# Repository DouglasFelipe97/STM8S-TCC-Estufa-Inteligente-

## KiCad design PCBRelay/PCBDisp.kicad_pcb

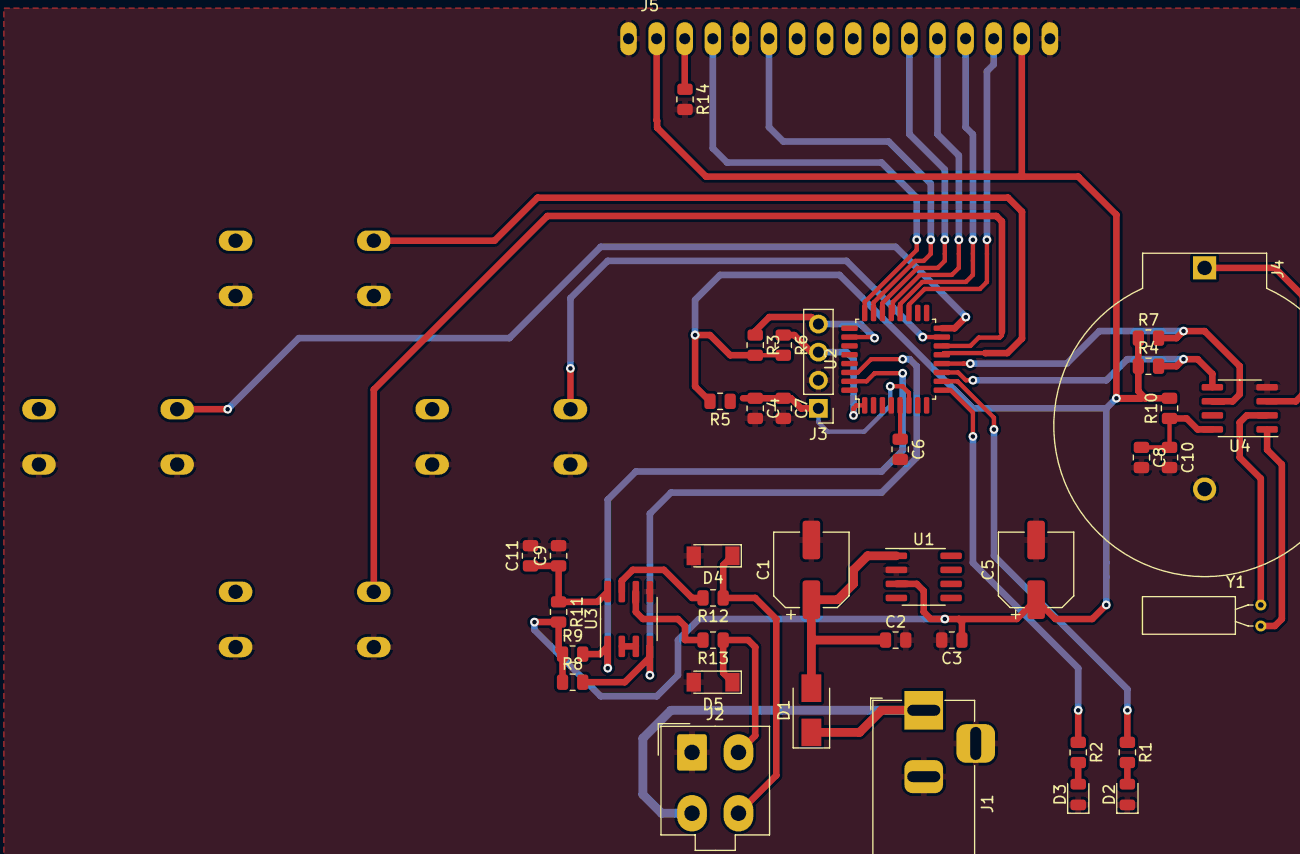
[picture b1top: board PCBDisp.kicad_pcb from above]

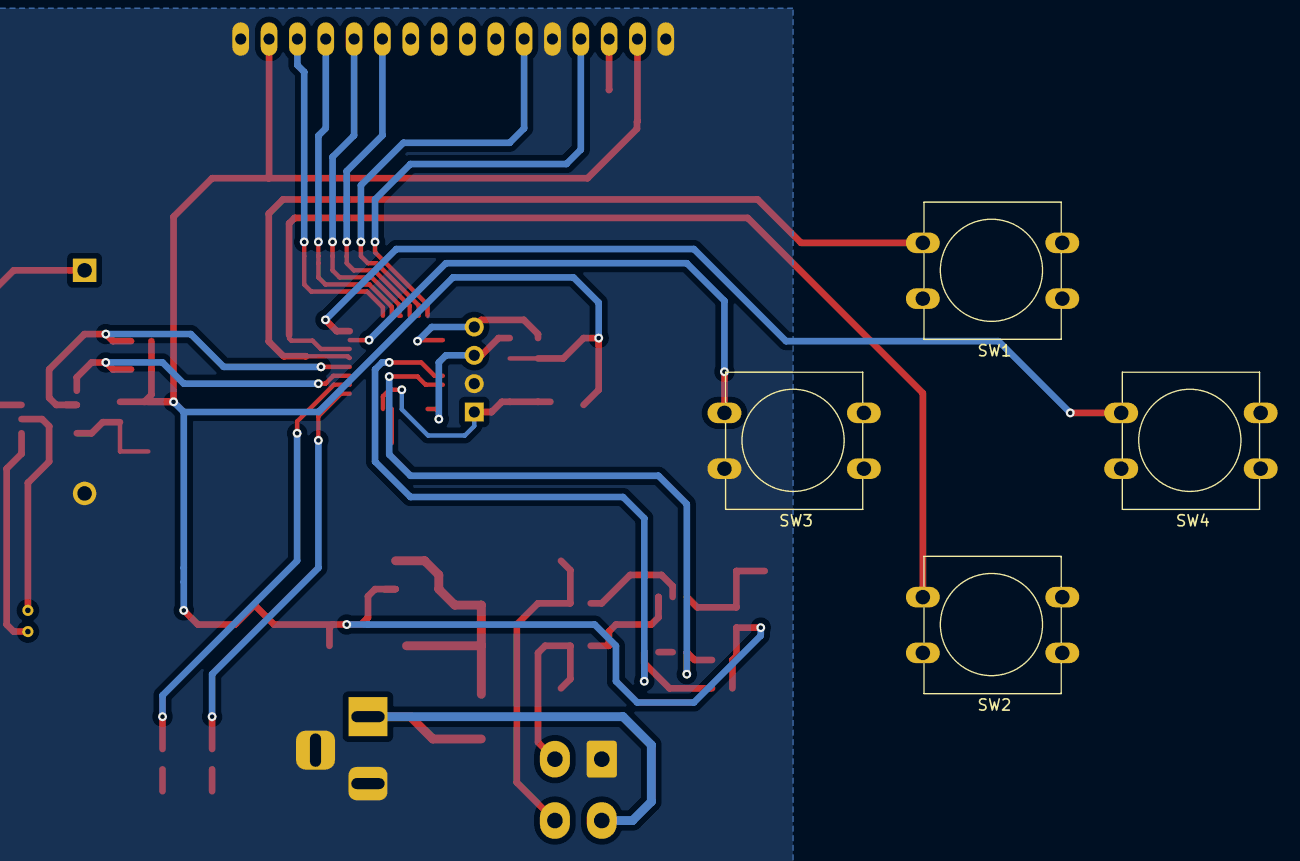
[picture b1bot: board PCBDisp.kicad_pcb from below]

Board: 2 copper layers, 44 parts (4 on the bottom side), 37 nets.

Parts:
C1, C5: 100uF 25V; CP_Elec_6.3x7.7
C2, C3, C7, C10, C11: 100nF; R_0805_2012Metric
C4, C8, C9: 4,7uF; R_0805_2012Metric
C6: 1uF; R_0805_2012Metric
D1: 1N4007; D_SMA
D2, D3: LED; LED_0805_2012Metric
D4, D5: 5V1; D_MiniMELF
J1: Barrel_Jack_Switch; P4_Macho
J2: Conn_02x02_Odd_Even; Molex_Mini-Fit_Jr_5566-04A_2x02_P4.20mm_Vertical
J3: Conn_01x04_Female; PinHeader_1x04_P2.54mm_Vertical
J4: Conn_01x02_Female; BatteryHolder_ComfortableElectronic_CH273-2450_1x2450
J5: Conn_01x16_Female; LCD-016Pads
R1, R2, R14: 1K; R_0805_2012Metric
R3, R6, R8, R9: 4K7; R_0805_2012Metric
R4, R7: 10K; R_0805_2012Metric
R5, R10, R11, R12, R13: 10R; R_0805_2012Metric
SW1: BTSOBE; SW_PUSH-12mm
SW2: BTDESCE; SW_PUSH-12mm
SW3: BTCONF; SW_PUSH-12mm
SW4: BTVOLTA; SW_PUSH-12mm
U1: L7805; SOIC-8_3.9x4.9mm_P1.27mm
U2: STM8S003K3T; LQFP-32_7x7mm_P0.8mm
U3: SN75176AD; SOIC-8_3.9x4.9mm_P1.27mm
U4: DS1307+; SOIC-8_3.9x4.9mm_P1.27mm
Y1: Crystal 32.768khz; Crystal_C38-LF_D3.0mm_L8.0mm_Horizontal

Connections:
/BTC: SW3.2, U2.15
/BTD: SW2.2, U2.14
/BTS: SW1.2, U2.13
/BTV: SW4.2, U2.16
/D4: J5.11, U2.22
/D5: J5.12, U2.21
/D6: J5.13, U2.20
/D7: J5.14, U2.19
/EN: J5.6, U2.23
/GRAV1: J3.3, R6.1, U2.1
/GRAV2: J3.4, R3.1, U2.26
/RS: J5.4, U2.24
/RX: R9.2, U2.31, U3.1
/SCL: R7.2, U2.12, U4.6
/SDA: R4.2, U2.11, U4.5
/TX: R8.2, U2.30, U3.4
/V0: J5.3, R14.1
/VCC: D1.1, J1.1, J2.3
/VDD: C3.1, C5.1, J5.2, J5.15, R3.2, R4.1, R5.2, R6.2, R7.1, R8.1, R9.1, R10.2, R11.2, U1.3
/VGRAV: C4.1, C7.1, J3.1, R5.1, U2.6
/VSS: C1.2, C2.2, C3.2, C4.2, C5.2, C6.2, C7.2, C8.2, C9.2, C10.2, C11.2, D2.1, D3.1, D4.2, D5.2, J1.2, J1.3, J2.1, J3.2, J4.2, J5.1, J5.5, J5.16, R14.2, SW1.1, SW2.1, SW3.1, SW4.1, U1.2, U2.4, U3.5, U4.4
unnamed: C1.1, C2.1, D1.2, U1.1
unnamed: C6.1, U2.5
unnamed: C8.1, C10.1, R10.1, U4.8
unnamed: C9.1, C11.1, R11.1, U3.8
unnamed: D2.2, R1.2
unnamed: D3.2, R2.2
unnamed: D4.1, J2.4, R12.1
unnamed: D5.1, J2.2, R13.1
unnamed: J4.1, U4.3
unnamed: R1.1, U2.10
unnamed: R2.1, U2.9
unnamed: R12.2, U3.7
unnamed: R13.2, U3.6
unnamed: U3.2, U3.3
unnamed: U4.1, Y1.2
unnamed: U4.2, Y1.1
